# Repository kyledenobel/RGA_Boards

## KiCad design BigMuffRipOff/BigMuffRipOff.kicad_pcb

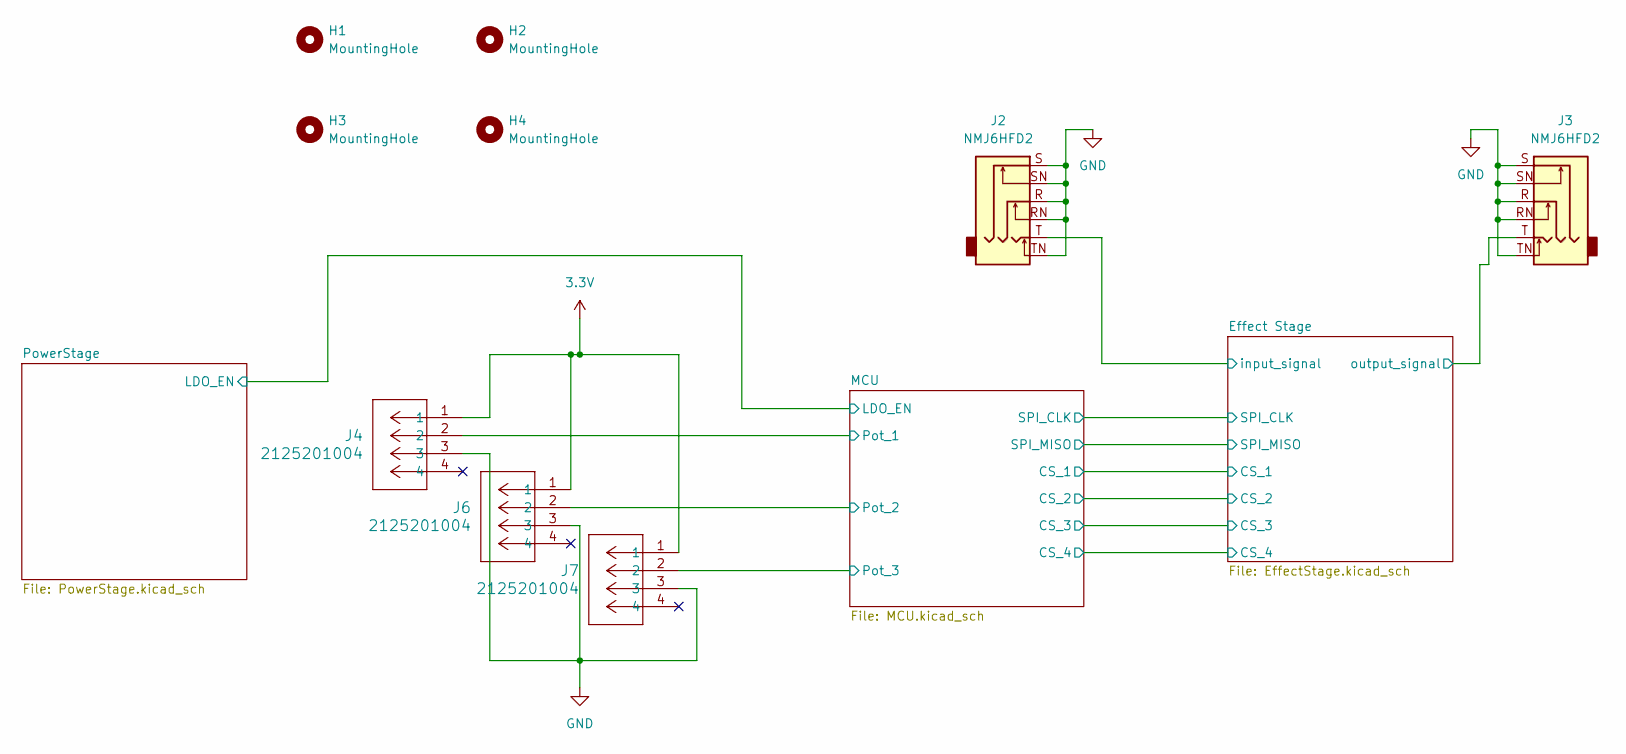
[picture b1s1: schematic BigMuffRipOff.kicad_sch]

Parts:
H1, H2, H3, H4: MountingHole; MountingHole_2.2mm_M2
J2, J3: NMJ6HFD2; Jack_6.35mm_Neutrik_NMJ6HFD2_Horizontal
J4, J6, J7: 2125201004; CONN_2125200001-SD_04_MOL

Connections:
3.3V: J4.1, J6.1, J7.1; also elsewhere on the board
/Effect Stage/input_signal: J2.T; also elsewhere on the board
/Effect Stage/output_signal: J3.T; also elsewhere on the board
/MCU/Pot_1: J4.2; also elsewhere on the board
/MCU/Pot_2: J6.2; also elsewhere on the board
/MCU/Pot_3: J7.2; also elsewhere on the board
GND: J2.R, J2.RN, J2.S, J2.SN, J2.TN, J3.R, J3.RN, J3.S, J3.SN, J3.TN, J4.3, J6.3, J7.3; also elsewhere on the board

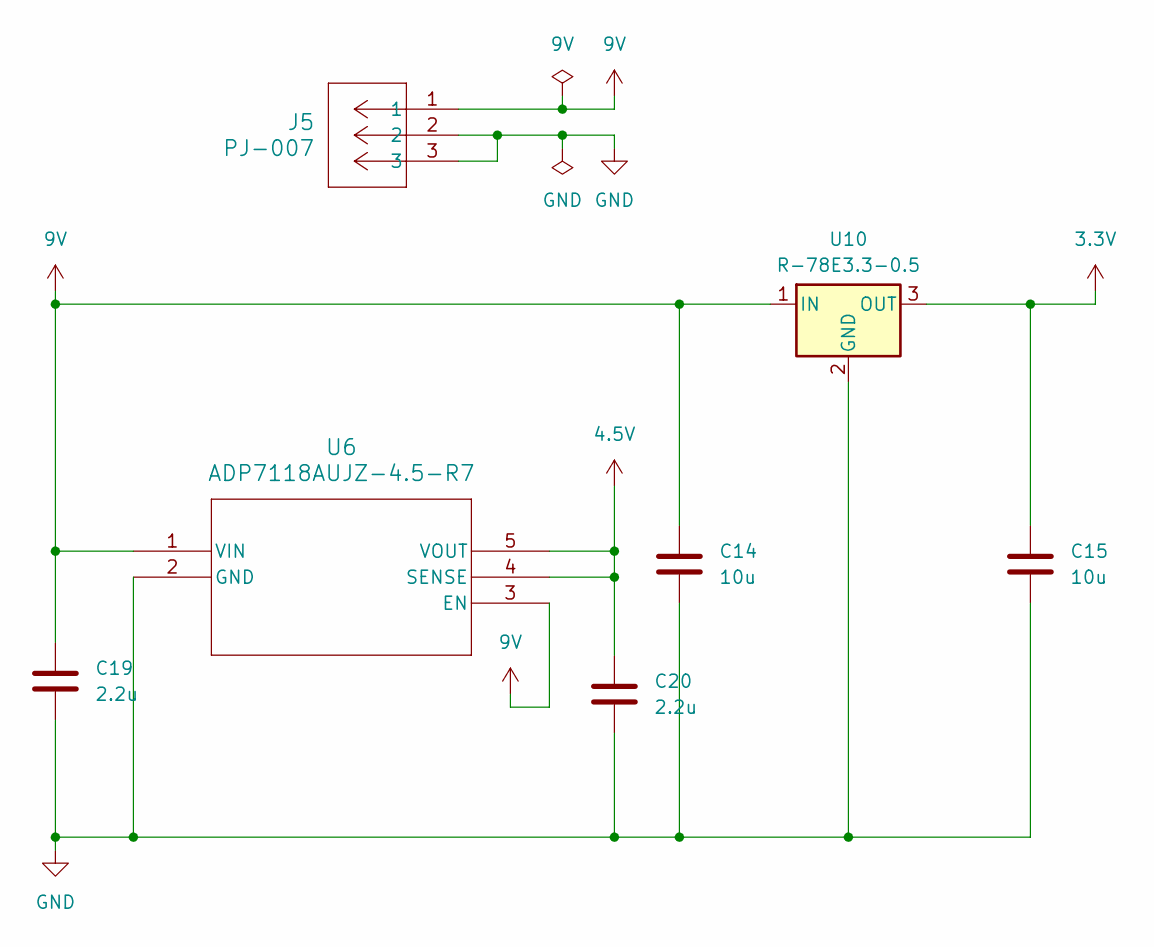
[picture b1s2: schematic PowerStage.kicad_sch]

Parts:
C14, C15: 10u; C_0603_1608Metric
C19, C20: 2.2u; C_0603_1608Metric
J5: PJ-007; CONN_PJ-007_SSD
U6: ADP7118AUJZ-4.5-R7; UJ-5_ADI
U10: R-78E3.3-0.5; Converter_DCDC_RECOM_R-78E-0.5_THT

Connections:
3.3V: C15.1, U10.3 (OUT); also elsewhere on the board
4.5V: C20.1, U6.4 (SENSE), U6.5 (VOUT); also elsewhere on the board
9V: C14.1, C19.1, J5.1, U6.1 (VIN), U6.3 (EN), U10.1 (IN); also elsewhere on the board
GND: C14.2, C15.2, C19.2, C20.2, J5.2, J5.3, U6.2 (GND), U10.2 (GND); also elsewhere on the board

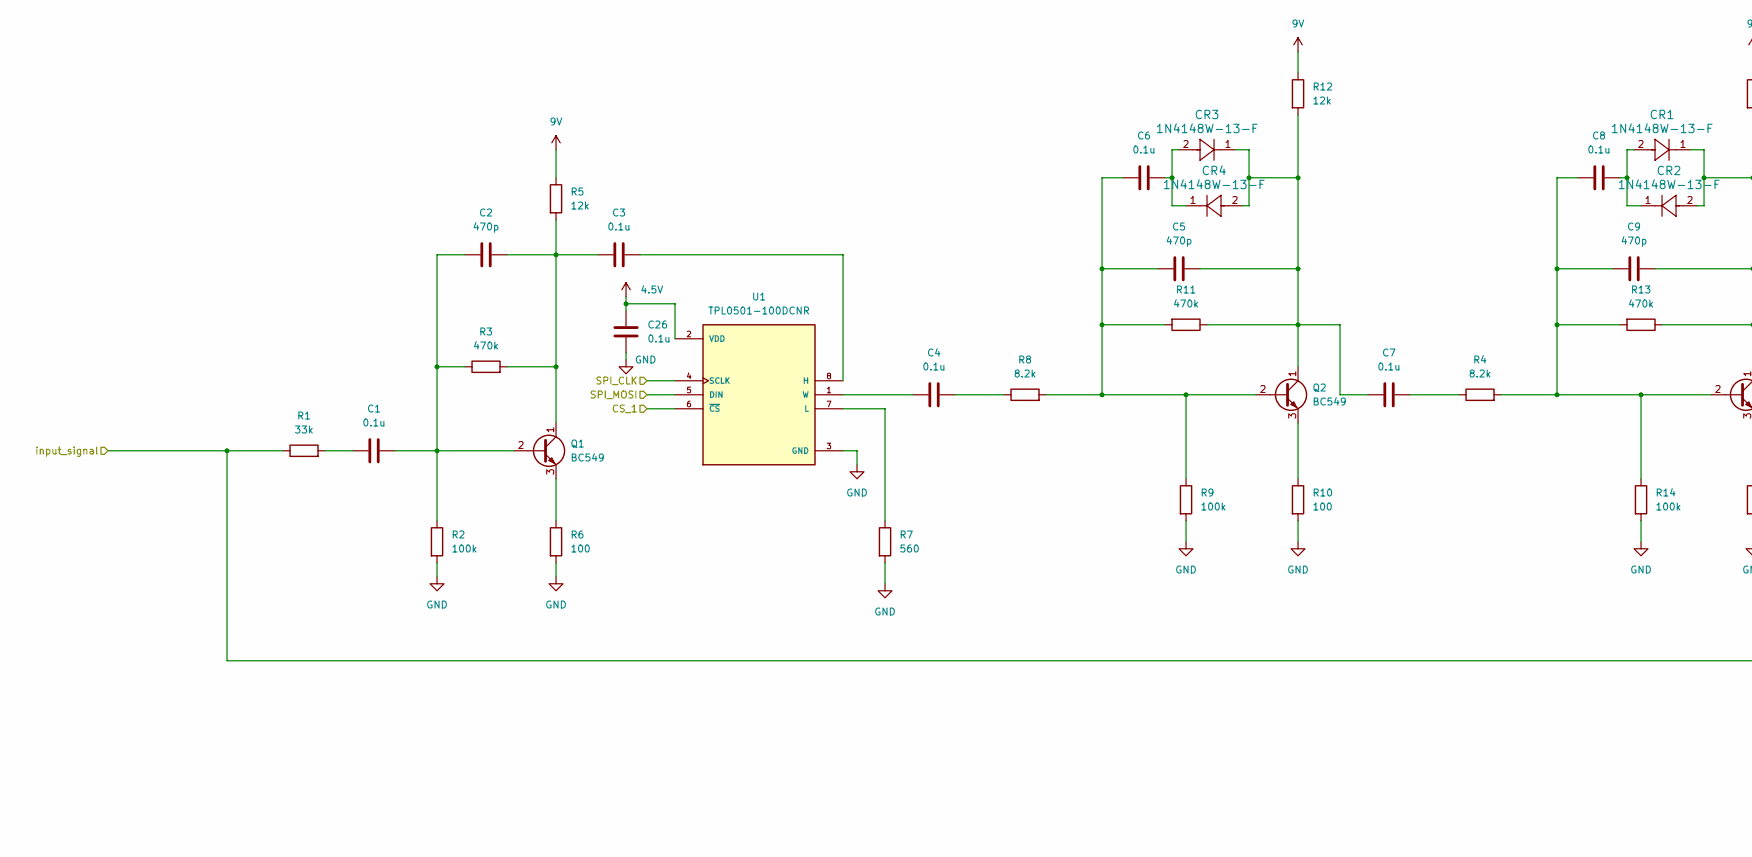
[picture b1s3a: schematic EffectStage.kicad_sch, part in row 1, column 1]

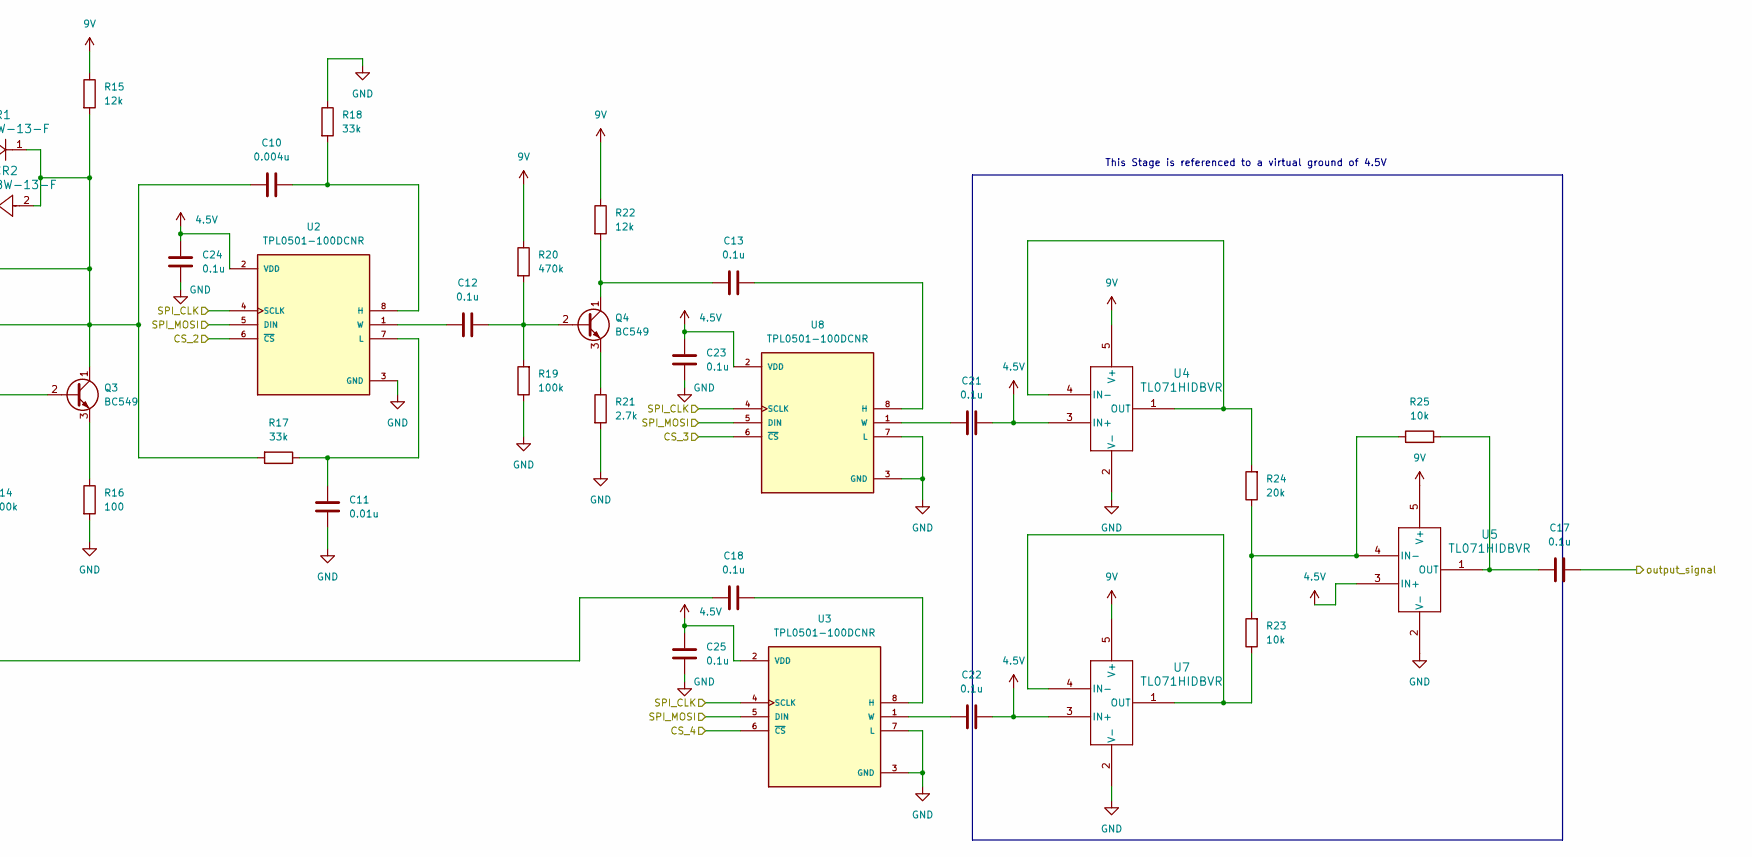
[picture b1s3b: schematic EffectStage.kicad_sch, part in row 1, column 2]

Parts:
C1, C3, C4, C6, C7, C8, C12, C13, C17, C18, C21, C22, C23, C24, C25, C26: 0.1u; C_0603_1608Metric
C2, C5, C9: 470p; C_0603_1608Metric
C10: 0.004u; C_0603_1608Metric
C11: 0.01u; C_0603_1608Metric
CR1, CR2, CR3, CR4: 1N4148W-13-F; SOD123_DIO
Q1, Q2, Q3, Q4: BC549; TO-92_Inline
R1, R17, R18: 33k; R_0603_1608Metric
R2, R9, R14, R19: 100k; R_0603_1608Metric
R3, R11, R13, R20: 470k; R_0603_1608Metric
R4, R8: 8.2k; R_0603_1608Metric
R5, R12, R15, R22: 12k; R_0603_1608Metric
R6, R10, R16: 100; R_0603_1608Metric
R7: 560; R_0603_1608Metric
R21: 2.7k; R_0603_1608Metric
R23, R25: 10k; R_0603_1608Metric
R24: 20k; R_0603_1608Metric
U1, U2, U3, U8: TPL0501-100DCNR; SOT65P280X145-8N; PARTREV C
U4, U5, U7: TL071HIDBVR; SOT23_DBV_5_TEX

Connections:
4.5V: C21.2, C22.2, C23.1, C24.1, C25.1, C26.1, U1.2 (VDD), U2.2 (VDD), U3.2 (VDD), U4.3 (IN+), U5.3 (IN+), U7.3 (IN+), U8.2 (VDD); also elsewhere on the board
9V: R5.1, R12.1, R15.1, R20.1, R22.1, U4.5 (V+), U5.5 (V+), U7.5 (V+); also elsewhere on the board
/Effect Stage/CS_1: U1.6 (~CS); also elsewhere on the board
/Effect Stage/CS_2: U2.6 (~CS); also elsewhere on the board
/Effect Stage/CS_3: U8.6 (~CS); also elsewhere on the board
/Effect Stage/CS_4: U3.6 (~CS); also elsewhere on the board
/Effect Stage/SPI_CLK: U1.4 (SCLK), U2.4 (SCLK), U3.4 (SCLK), U8.4 (SCLK); also elsewhere on the board
/Effect Stage/SPI_MOSI: U1.5 (DIN), U2.5 (DIN), U3.5 (DIN), U8.5 (DIN); also elsewhere on the board
/Effect Stage/input_signal: C18.2, R1.1; also elsewhere on the board
/Effect Stage/output_signal: C17.1; also elsewhere on the board
GND: C11.2, C23.2, C24.2, C25.2, C26.2, R2.2, R6.2, R7.2, R9.2, R10.2, R14.2, R16.2, R18.1, R19.1, R21.2, U1.3 (GND), U2.3 (GND), U3.3 (GND), U3.7 (L), U4.2 (V-), U5.2 (V-), U7.2 (V-), U8.3 (GND), U8.7 (L); also elsewhere on the board
unnamed: C1.2, R1.2
unnamed: C4.1, R8.1
unnamed: C6.1, CR3.2, CR4.1
unnamed: C7.1, R4.1
unnamed: C8.1, CR1.2, CR2.1
unnamed: C1.1, C2.2, Q1.2 (B), R2.1, R3.1
unnamed: C2.1, C3.2, Q1.1 (C), R3.2, R5.2
unnamed: Q1.3 (E), R6.1
unnamed: C5.2, C6.2, Q2.2 (B), R8.2, R9.1, R11.2
unnamed: C5.1, C7.2, CR3.1, CR4.2, Q2.1 (C), R11.1, R12.2
unnamed: Q2.3 (E), R10.1
unnamed: C8.2, C9.2, Q3.2 (B), R4.2, R13.2, R14.1
unnamed: C9.1, C10.2, CR1.1, CR2.2, Q3.1 (C), R13.1, R15.2, R17.2
unnamed: Q3.3 (E), R16.1
unnamed: C12.1, Q4.2 (B), R19.2, R20.2
unnamed: C13.2, Q4.1 (C), R22.2
unnamed: Q4.3 (E), R21.1
unnamed: C3.1, U1.8 (H)
unnamed: R7.1, U1.7 (L)
unnamed: C4.2, U1.1 (W)
unnamed: C10.1, R18.2, U2.8 (H)
unnamed: C11.1, R17.1, U2.7 (L)
unnamed: C12.2, U2.1 (W)
unnamed: C18.1, U3.8 (H)
unnamed: C22.1, U3.1 (W)
unnamed: R24.2, U4.1 (OUT), U4.4 (IN-)
unnamed: R23.2, R24.1, R25.1, U5.4 (IN-)
unnamed: C17.2, R25.2, U5.1 (OUT)
unnamed: R23.1, U7.1 (OUT), U7.4 (IN-)
unnamed: C13.1, U8.8 (H)
unnamed: C21.1, U8.1 (W)

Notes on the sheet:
This Stage is referenced to a virtual ground of 4.5V

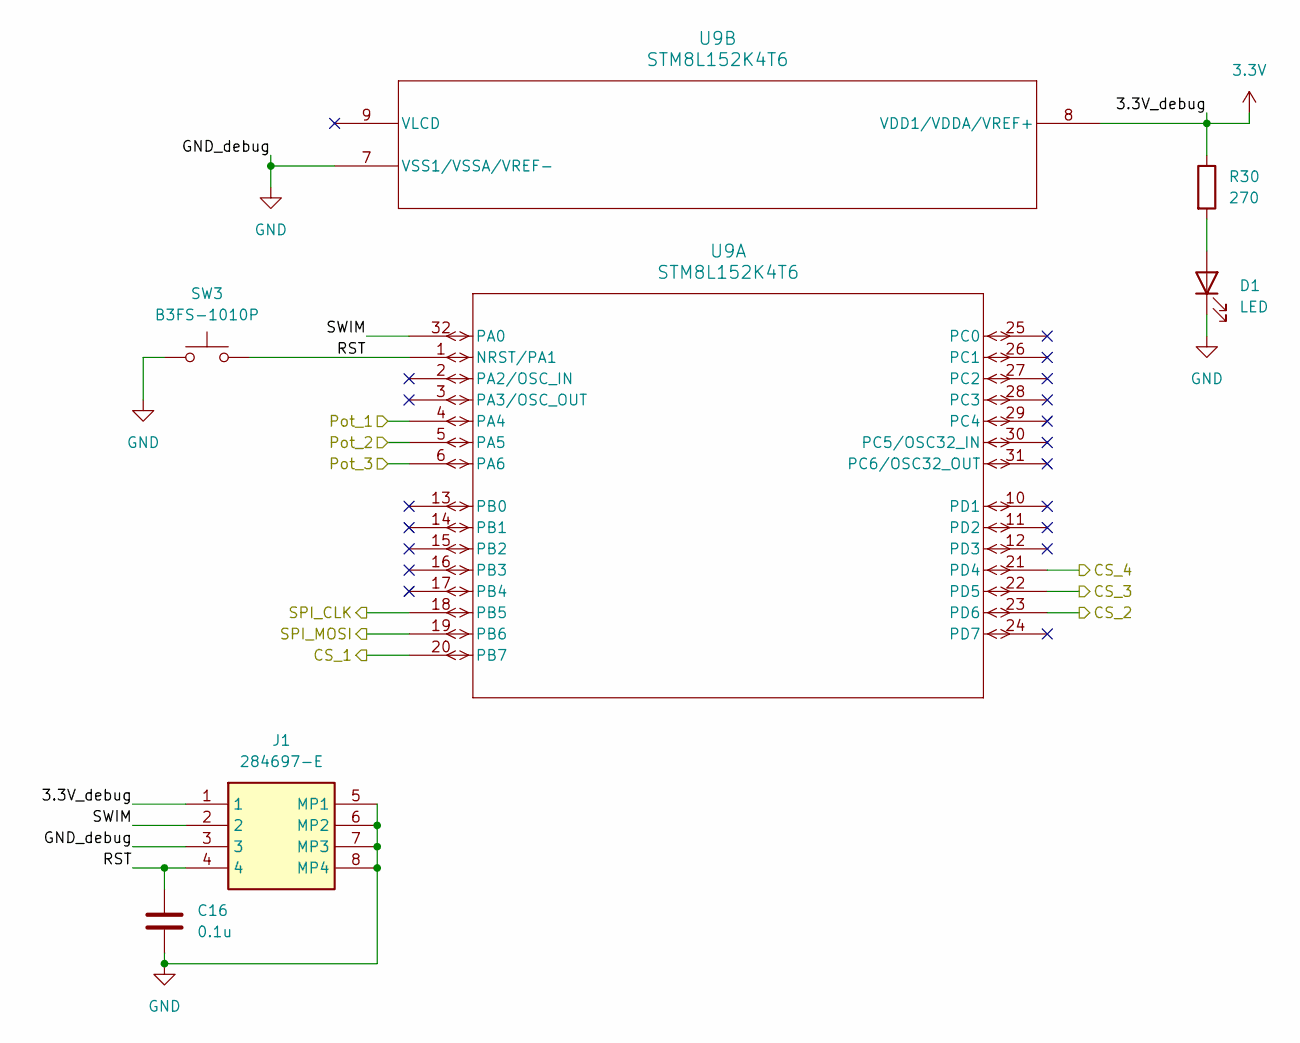
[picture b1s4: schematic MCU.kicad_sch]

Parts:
C16: 0.1u; C_0603_1608Metric
D1: LED; LED_0603_1608Metric
J1: 284697-E; 284697E; Mouser Part Number 305-284697
R30: 270; R_0603_1608Metric
SW3: B3FS-1010P; SW_SPST_Omron_B3FS-101xP
U9: STM8L152K4T6; LQFP-32

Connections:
3.3V: J1.1, R30.1, U9.8 (VDD1/VDDA/VREF+), U9.9 (VLCD); also elsewhere on the board
/Effect Stage/CS_1: U9.20 (PB7); also elsewhere on the board
/Effect Stage/CS_2: U9.23 (PD6); also elsewhere on the board
/Effect Stage/CS_3: U9.22 (PD5); also elsewhere on the board
/Effect Stage/CS_4: U9.21 (PD4); also elsewhere on the board
/Effect Stage/SPI_CLK: U9.18 (PB5); also elsewhere on the board
/Effect Stage/SPI_MOSI: U9.19 (PB6); also elsewhere on the board
/MCU/Pot_1: U9.4 (PA4); also elsewhere on the board
/MCU/Pot_2: U9.5 (PA5); also elsewhere on the board
/MCU/Pot_3: U9.6 (PA6); also elsewhere on the board
/MCU/RST: C16.1, J1.4, SW3.2, U9.1 (NRST/PA1)
/MCU/SWIM: J1.2, U9.32 (PA0)
/MCU/UART_RX: U9.27 (PC2); also elsewhere on the board
/MCU/UART_TX: U9.28 (PC3); also elsewhere on the board
GND: C16.2, D1.1 (K), J1.3, J1.5 (MP1), J1.6 (MP2), J1.7 (MP3), J1.8 (MP4), SW3.1, U9.7 (VSS1/VSSA/VREF-); also elsewhere on the board
unnamed: D1.2 (A), R30.2

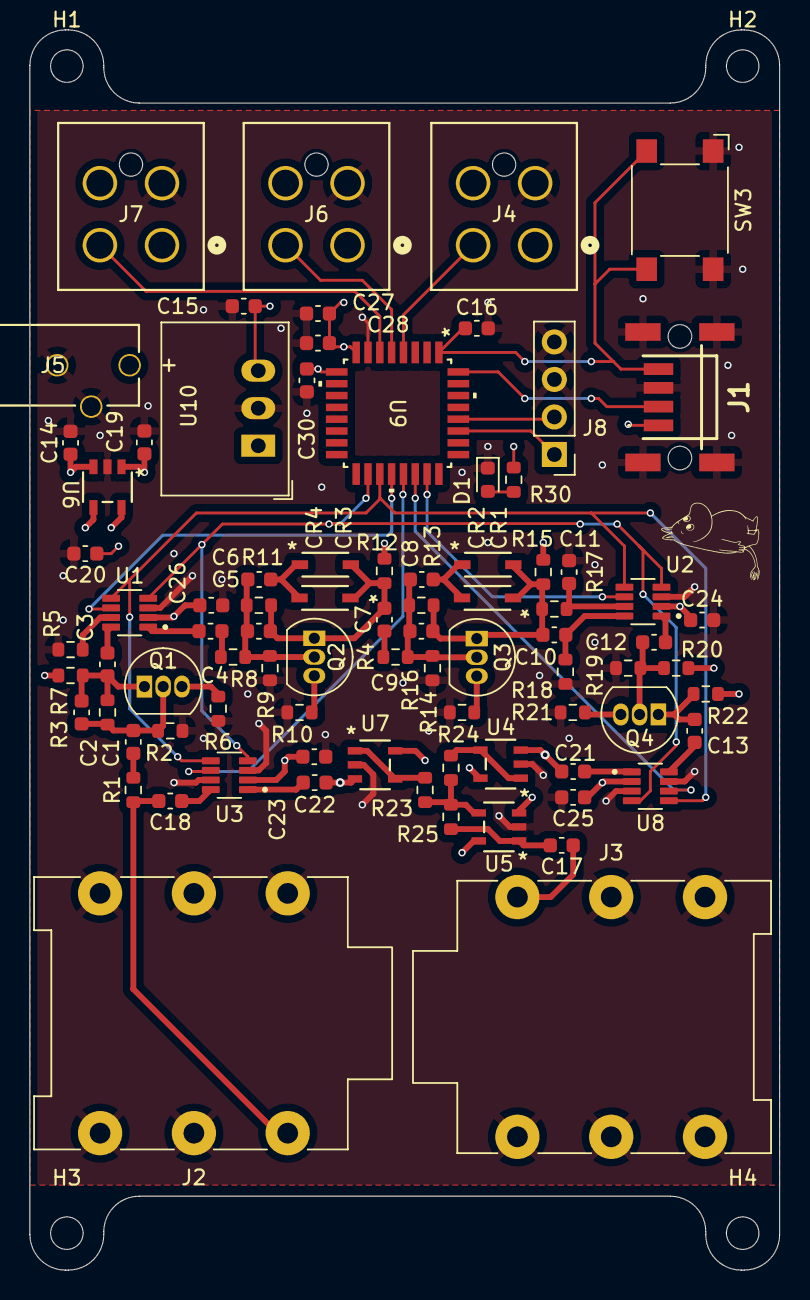
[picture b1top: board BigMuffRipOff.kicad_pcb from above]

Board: 4 copper layers, 50.8 x 84.0 mm, 87 parts (0 on the bottom side), 51 nets.

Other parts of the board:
C27: 10n; C_0603_1608Metric
C28: 100n; C_0603_1608Metric
C30: 1u; C_0603_1608Metric
J8: Conn_01x04; PinHeader_1x04_P2.54mm_Vertical

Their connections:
3.3V: C27.1, C28.1, C30.2; also elsewhere on the board
/MCU/UART_RX: J8.1; also elsewhere on the board
/MCU/UART_TX: J8.2; also elsewhere on the board
GND: C27.2, C28.2, C30.1, J8.3, J8.4; also elsewhere on the board

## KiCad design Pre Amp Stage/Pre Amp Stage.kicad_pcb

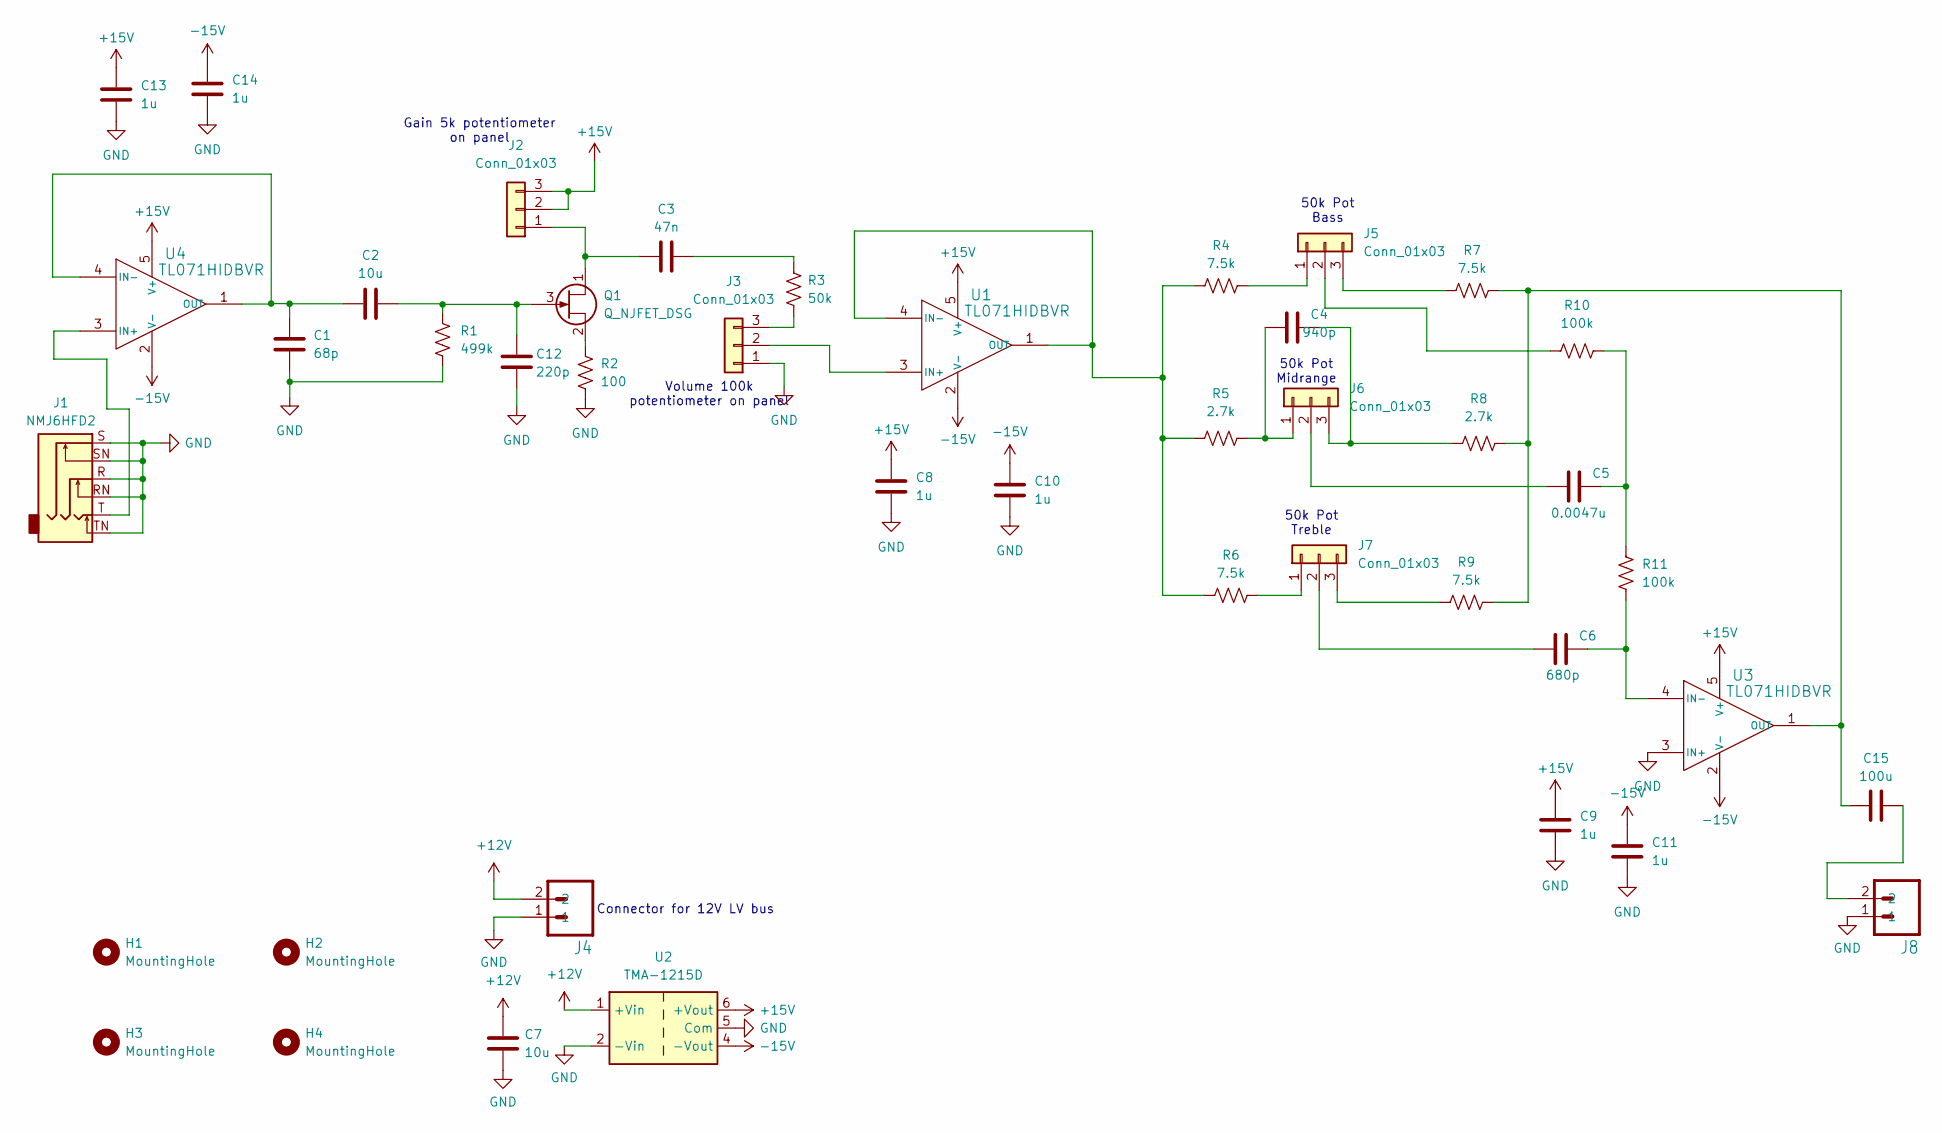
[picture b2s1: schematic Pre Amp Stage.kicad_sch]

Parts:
C1: 68p; R_0603_1608Metric
C2, C7: 10u; R_0603_1608Metric
C3: 47n; R_0603_1608Metric
C4: 940p; R_0603_1608Metric
C5: 0.0047u; R_0603_1608Metric
C6: 680p; R_0603_1608Metric
C8, C9, C10, C11, C13, C14: 1u; R_0603_1608Metric
C12: 220p; R_0603_1608Metric
C15: 100u; R_0805_2012Metric_Pad1.20x1.40mm_HandSolder
H1, H2, H3, H4: MountingHole; MountingHole_2.2mm_M2
J1: NMJ6HFD2; Jack_6.35mm_Neutrik_NMJ6HFD2_Horizontal
J2, J3, J5, J6, J7: Conn_01x03; Molex_Micro-Fit_3.0_43650-0315_1x03_P3.00mm_Vertical
J4, J8: MINIFIT-2-VERT; Molex_Mini-Fit_Jr_5566-02A_2x01_P4.20mm_Vertical
Q1: Q_NJFET_DSG; TO-92_Inline
R1: 499k; R_0603_1608Metric
R2: 100; R_0603_1608Metric
R3: 50k; R_0603_1608Metric
R4, R6, R7, R9: 7.5k; R_0603_1608Metric
R5, R8: 2.7k; R_0603_1608Metric
R10, R11: 100k; R_0603_1608Metric
U1, U3, U4: TL071HIDBVR; TL071
U2: TMA-1215D; Converter_DCDC_TRACO_TMA-05xxD_12xxD_Dual_THT

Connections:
+12V: C7.1, J4.2, U2.1 (+Vin)
+15V: C8.1, C9.1, C13.1, J2.2, J2.3, U1.5 (V+), U2.6 (+Vout), U3.5 (V+), U4.5 (V+)
-15V: C10.1, C11.1, C14.1, U1.2 (V-), U2.4 (-Vout), U3.2 (V-), U4.2 (V-)
GND: C1.2, C7.2, C8.2, C9.2, C10.2, C11.2, C12.2, C13.2, C14.2, J1.R, J1.RN, J1.S, J1.SN, J1.TN, J3.1, J4.1, J8.1, R1.2, R2.2, U2.2 (-Vin), U2.5 (Com), U3.3 (IN+)
unnamed: C3.2, R3.1
unnamed: C5.1, R10.2, R11.2
unnamed: C15.2, J8.2
unnamed: C3.1, J2.1, Q1.1 (D)
unnamed: J3.2, U1.3 (IN+)
unnamed: J3.3, R3.2
unnamed: J5.1, R4.2
unnamed: J5.2, R10.1
unnamed: J5.3, R7.1
unnamed: C4.2, J6.1, R5.2
unnamed: C5.2, J6.2
unnamed: C4.1, J6.3, R8.1
unnamed: J7.1, R6.2
unnamed: C6.2, J7.2
unnamed: J7.3, R9.1
unnamed: C2.2, C12.1, Q1.3 (G), R1.1
unnamed: Q1.2 (S), R2.1
unnamed: R4.1, R5.1, R6.1, U1.1 (OUT), U1.4 (IN-)
unnamed: C6.1, R11.1, U3.4 (IN-)
unnamed: C15.1, R7.2, R8.2, R9.2, U3.1 (OUT)
unnamed: J1.T, U4.3 (IN+)
unnamed: C1.1, C2.1, U4.1 (OUT), U4.4 (IN-)

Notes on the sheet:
50k Pot Bass
Gain 5k potentiometer on panel
Connector for 12V LV bus
Volume 100k potentiometer on panel
50k Pot Treble
50k Pot Midrange

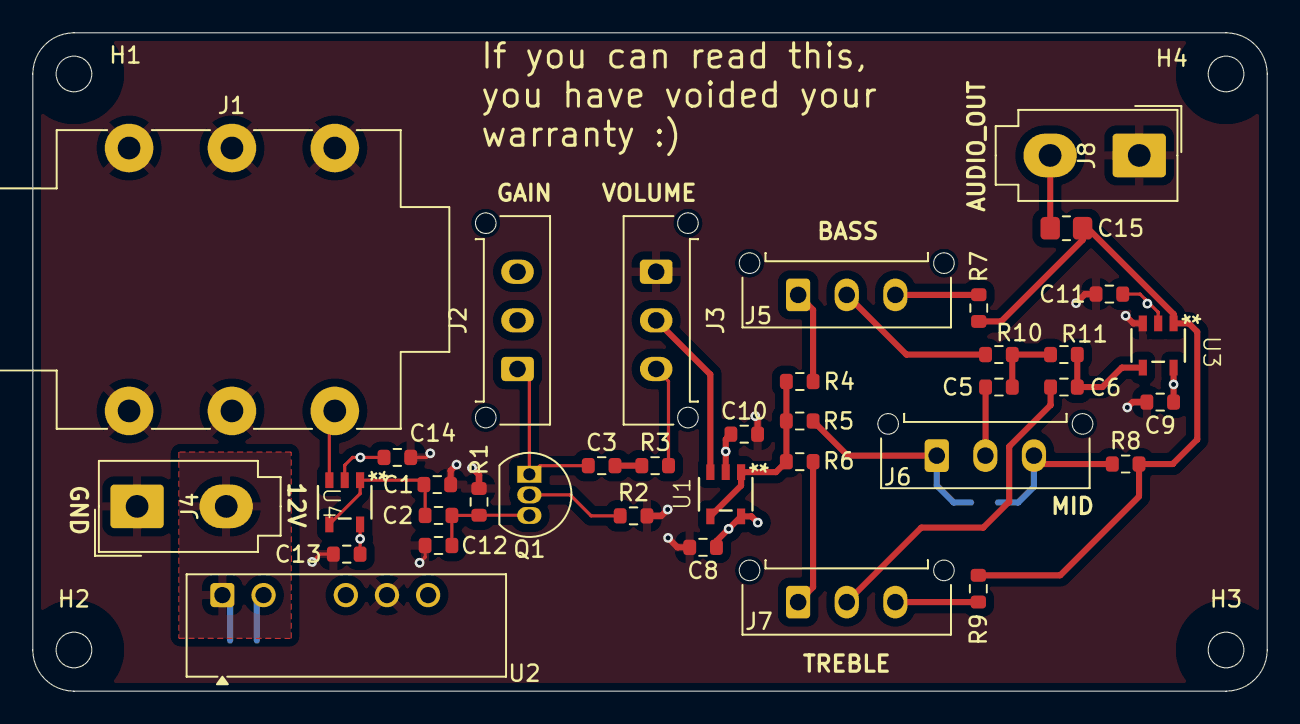
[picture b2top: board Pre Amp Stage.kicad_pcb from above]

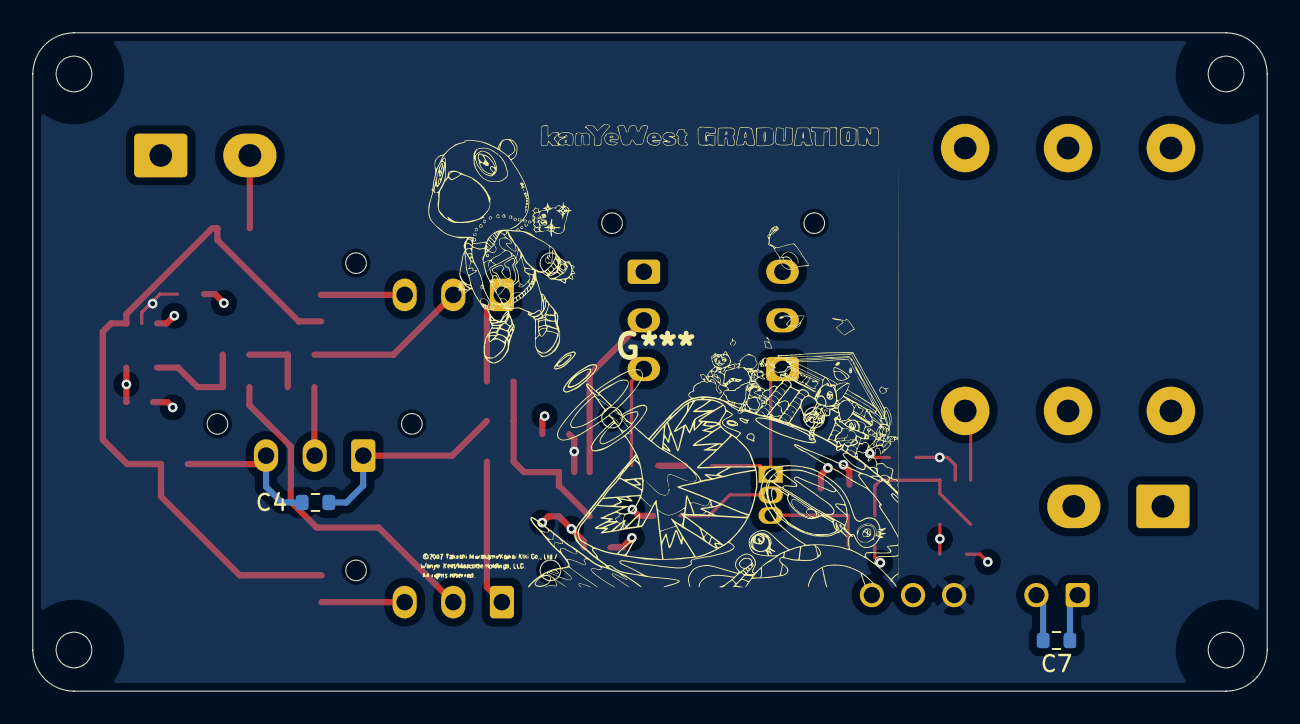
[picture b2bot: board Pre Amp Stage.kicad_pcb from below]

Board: 4 copper layers, 76.2 x 40.6 mm, 43 parts (2 on the bottom side), 26 nets.
